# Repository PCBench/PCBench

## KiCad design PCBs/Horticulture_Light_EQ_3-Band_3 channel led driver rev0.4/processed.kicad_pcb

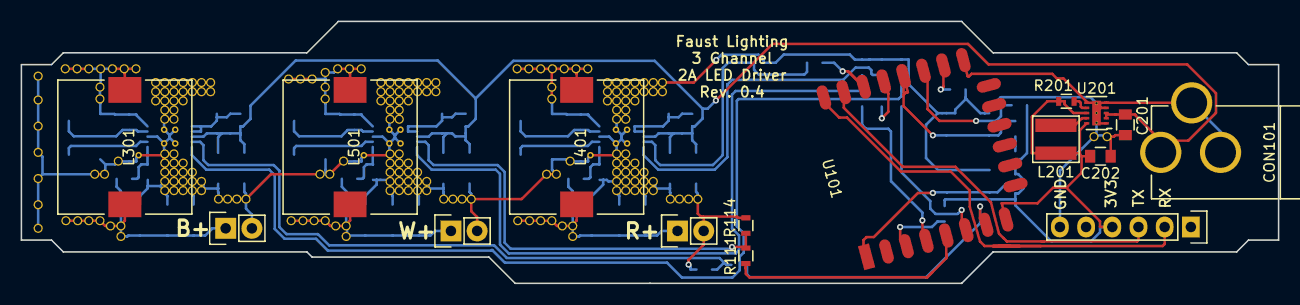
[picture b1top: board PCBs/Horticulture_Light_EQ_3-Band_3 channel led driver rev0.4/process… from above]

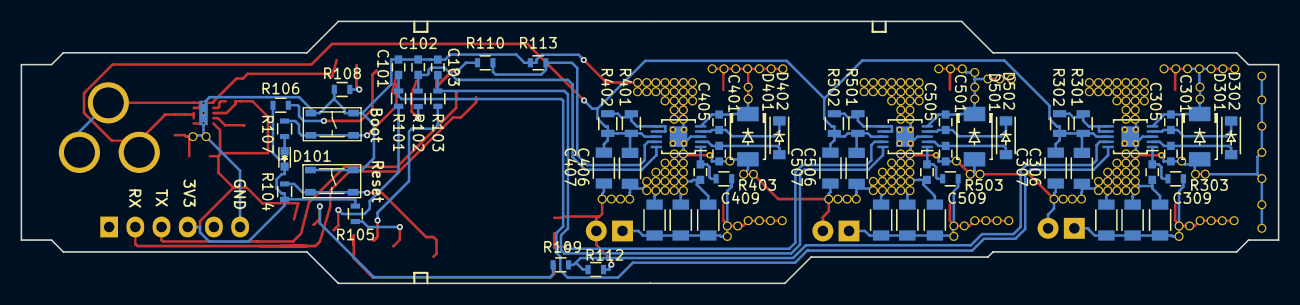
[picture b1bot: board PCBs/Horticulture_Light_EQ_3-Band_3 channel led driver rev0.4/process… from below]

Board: 2 copper layers, 121.9 x 25.4 mm, 76 parts (60 on the bottom side), 42 nets.

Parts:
C101, C102, C103: 10uF; C_0603
C201: 2.2uF; C_0805
C202: 22.0uF; C_0805
C301, C401, C501: 0.1uF; C_0603
C302, C303, C304, C306, C307, C402, C403, C404, C406, C407, C502, C503, C504, C506, C507: 2.2uF; C_1206
C305, C405, C505: 1uF; C_0603
C309, C409, C509: 470pF; C_0603
CON101: BARREL_JACK; Barrel_Jack_Wurth_694106301002
D101: LED; LED-0603
D301, D401, D501: 100V 3A; SOD-128-2
D302, D402, D502: 100V 200mA; SOD-123
L201: 10uH; VLS4012ET-100M
L301, L401, L501: 47uH; MBH12575C
P1, P2, P3: CONN_01X02; Pin_Header_Straight_1x02
P101: CONN_01X06; Pin_Header_Straight_1x06
R101, R102, R103, R107, R109, R110, R111: 1K; R_0603
R104, R105, R106, R108, R112, R113, R114: 10K; R_0603
R201: 100K; R_0603
R301, R302, R401, R402, R501, R502: 0.27; R_0805
R303, R403, R503: 48.7k; R_0603
SW101, SW102: TACT_4.2MM; MF_Switches-TACT4.2MM
U101: ESP8266-12E; ESP-12E
U201: TPS62177
U301, U401, U501: TPS92515; TPS92515x

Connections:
3V3: C202.1, D101.2, L201.2, P101.4, R104.2, R105.2, R106.2, R201.1, U101.8, U201.8, U201.10
+24V: C201.1, C306.1, C307.1, C406.1, C407.1, C506.1, C507.1, CON101.1, R301.1, R302.1, R401.1, R402.1, R501.1, R502.1, U201.2, U201.3, U301.8, U401.8, U501.8
/BOOT: R107.1, SW101.P$1, SW101.P$2, U101.18
/Blue_1.5A_Set/Analog_Control: C101.1, R101.1, U301.10
/Blue_1.5A_Set/PWM_Control: R109.2, R112.2, U301.9
/ENABLE: R105.1, U101.3
/GPIO2: R106.1, U101.17
/GPIO15: R108.2, U101.16
/RESET: R104.1, SW102.P$1, SW102.P$2, U101.1
/RX: P101.3, U101.21
/Red_1.5A_Set/Analog_Control: C102.1, R102.1, U401.10
/Red_1.5A_Set/PWM_Control: R110.2, R113.2, U401.9
/TX: P101.2, U101.22
/White_1.5A_Set/Analog_Control: C103.1, R103.1, U501.10
/White_1.5A_Set/PWM_Control: R111.2, R114.2, U501.9
BDIM: R101.2, U101.6
BLED+: C302.1, C303.1, C304.1, L301.1, P1.1, R303.2
BLED-: C101.2, C102.2, C103.2, C201.2, C202.2, C302.2, C303.2, C304.2, C305.1, C306.2, C307.2, C309.2, C402.2, C403.2, C404.2, C405.1, C406.2, C407.2, C409.2, C502.2, C503.2, C504.2, C505.1, C506.2, C507.2, C509.2, CON101.2, CON101.3, D301.2, D401.2, D501.2, P1.2, P2.2, P3.2, P101.6, R108.1, R112.1, R113.1, R114.1, SW101.P$3, SW101.P$4, SW102.P$3, SW102.P$4, U101.15, U201.1, U201.4, U201.5, U201.6, U201.11, U301.3, U301.11, U401.3, U401.11, U501.3, U501.11
BPWM: R109.1, U101.7
unnamed: C301.1, D301.1, L301.2, U301.5
unnamed: C301.2, D302.1, U301.4
unnamed: C305.2, D302.2, U301.2
unnamed: C309.1, R303.1, U301.1
unnamed: C401.1, D401.1, L401.2, U401.5
unnamed: C401.2, D402.1, U401.4
unnamed: C405.2, D402.2, U401.2
unnamed: C409.1, R403.1, U401.1
unnamed: C501.1, D501.1, L501.2, U501.5
unnamed: C501.2, D502.1, U501.4
unnamed: C505.2, D502.2, U501.2
unnamed: C509.1, R503.1, U501.1
unnamed: L201.1, U201.9
unnamed: R201.2, U201.7
unnamed: R301.2, R302.2, U301.6, U301.7
unnamed: R401.2, R402.2, U401.6, U401.7
unnamed: R501.2, R502.2, U501.6, U501.7
RDIM: R102.2, U101.19
RLED+: C402.1, C403.1, C404.1, L401.1, P2.1, R403.2
RPWM: R110.1, U101.20
WDIM: R103.2, U101.4
WLED+: C502.1, C503.1, C504.1, L501.1, P3.1, R503.2
WPWM: R111.1, U101.5

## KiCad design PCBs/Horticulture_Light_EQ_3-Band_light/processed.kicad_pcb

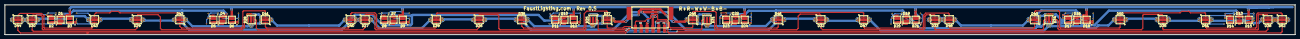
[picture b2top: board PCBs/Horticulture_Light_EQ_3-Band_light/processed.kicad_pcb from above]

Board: 2 copper layers, 551.2 x 12.7 mm, 53 parts (0 on the bottom side), 47 nets.

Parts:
D1, D2, D3, D4, D5, D6, D7, D8, D9, D10, D11, D12, D13, D14, D15, D16, D17, D18, D19, D20, D21, D22, D23, D24: Led_Small; MP3030
D25, D26, D27, D28, D29, D30, D31, D32, D33, D34, D35, D36: Blue 450nm; Blue_450nm
D37, D38, D39, D40, D41, D42, D43, D44, D45, D46, D47, D48, D49, D50, D51, D52: Deep Red 660nm; Deep_Red_660nm
P1: CONN_02X03; 1814676

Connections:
B+: D25.2, D31.2, P1.5
B-: D30.1, D36.1, P1.6
unnamed: D1.1, D2.2
unnamed: D2.1, D3.2
unnamed: D4.1, D5.2
unnamed: D5.1, D6.2
unnamed: D7.1, D8.2
unnamed: D8.1, D9.2
unnamed: D10.1, D11.2
unnamed: D11.1, D12.2
unnamed: D13.1, D14.2
unnamed: D14.1, D15.2
unnamed: D16.1, D17.2
unnamed: D17.1, D18.2
unnamed: D19.1, D20.2
unnamed: D20.1, D21.2
unnamed: D22.1, D23.2
unnamed: D23.1, D24.2
unnamed: D25.1, D26.2
unnamed: D26.1, D27.2
unnamed: D27.1, D28.2
unnamed: D28.1, D29.2
unnamed: D29.1, D30.2
unnamed: D31.1, D32.2
unnamed: D32.1, D33.2
unnamed: D33.1, D34.2
unnamed: D34.1, D35.2
unnamed: D35.1, D36.2
unnamed: D37.1, D38.2
unnamed: D38.1, D39.2
unnamed: D39.1, D40.2
unnamed: D40.1, D41.2
unnamed: D41.1, D42.2
unnamed: D42.1, D43.2
unnamed: D43.1, D44.2
unnamed: D45.1, D46.2
unnamed: D46.1, D47.2
unnamed: D47.1, D48.2
unnamed: D48.1, D49.2
unnamed: D49.1, D50.2
unnamed: D50.1, D51.2
unnamed: D51.1, D52.2
R+: D37.2, D45.2, P1.1
R-: D44.1, D52.1, P1.2
THERMAL: D25.3, D26.3, D27.3, D28.3, D29.3, D30.3, D31.3, D32.3, D33.3, D34.3, D35.3, D36.3, D37.3, D38.3, D39.3, D40.3, D41.3, D42.3, D43.3, D44.3, D45.3, D46.3, D47.3, D48.3, D49.3, D50.3, D51.3, D52.3
W+: D1.2, D4.2, D7.2, D10.2, D13.2, D16.2, D19.2, D22.2, P1.3
W-: D3.1, D6.1, D9.1, D12.1, D15.1, D18.1, D21.1, D24.1, P1.4

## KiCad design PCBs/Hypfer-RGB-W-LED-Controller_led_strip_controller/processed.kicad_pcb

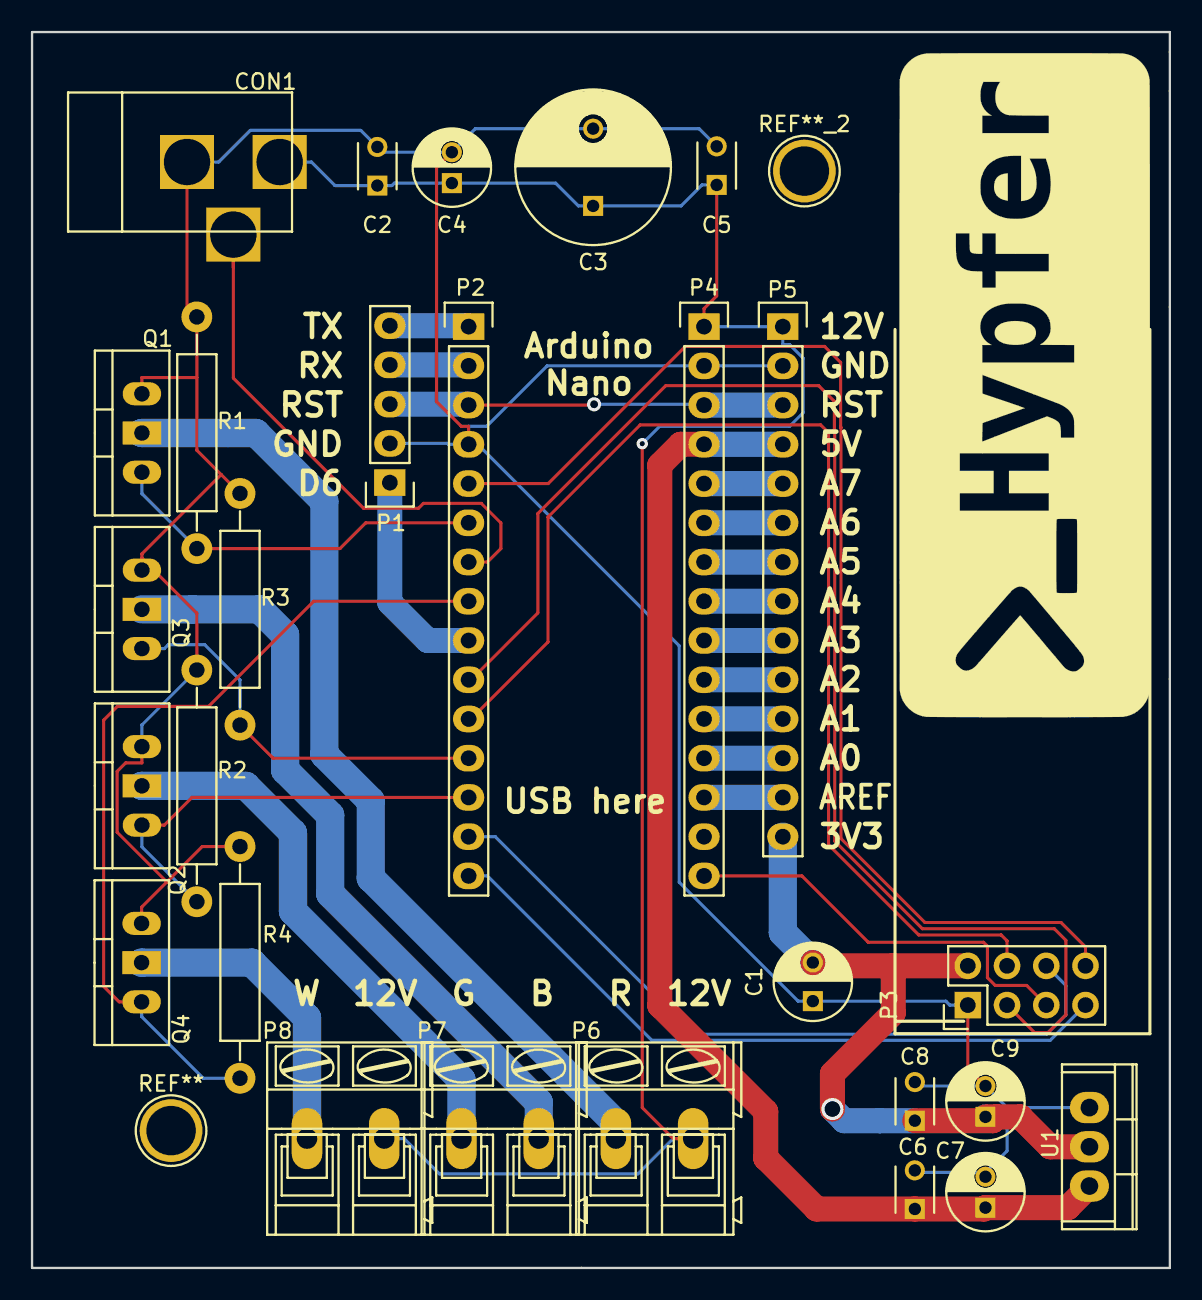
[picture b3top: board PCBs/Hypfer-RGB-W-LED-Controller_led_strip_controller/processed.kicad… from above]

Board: 2 copper layers, 73.7 x 80.0 mm, 27 parts (0 on the bottom side), 32 nets.

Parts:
C1: 1uF; C_Radial_D5_L11_P2.5
C2, C5, C6, C8: 100nF; C_Disc_D3_P2.5
C3: 1000uF; C_Radial_D10_L20_P5
C4, C7, C9: 47uF; C_Radial_D5_L11_P2
CON1: BARREL_JACK
P1: CONN_01X05; Socket_Strip_Straight_1x05
P2, P4: CONN_01X15; Socket_Strip_Straight_1x15
P3: CONN_02X04; Pin_Header_Straight_2x04
P5: CONN_01X14; Socket_Strip_Straight_1x14
P6, P7, P8: CONN_01X02; AK300-2
Q1, Q2, Q3, Q4: Q_NMOS_GDS; Diode_TO-220_Dual_CommonCathode_Vertical
R1, R2, R3, R4: 10k; Resistor_Horizontal_RM15mm
U1: AP1117; TO-220

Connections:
+3V3: C1.2, C8.1, C9.1, P3.2, P5.14, U1.2
+5V: C6.1, C7.1, P4.4, P5.4, U1.3
+12V: C2.1, C3.1, C4.1, C5.1, CON1.1, P4.1, P5.1, P6.2, P8.2
/ADC0: P4.12, P5.12
/ADC1: P4.11, P5.11
/ADC2: P4.10, P5.10
/ADC3: P4.9, P5.9
/ADC4: P4.8, P5.8
/ADC5: P4.7, P5.7
/ADC6: P4.6, P5.6
/ADC7: P4.5, P5.5
/AREF: P4.13, P5.13
/D6: P1.1, P2.9
/RESET: P1.3, P2.3, P4.3, P5.3
/RX: P1.4, P2.2
/TX: P1.5, P2.1
FET_B: P2.12, Q3.1, R3.1
FET_G: P2.13, Q2.1, R2.1
FET_R: P2.6, Q1.1, R1.1
FET_W: P2.8, Q4.1, R4.1
GND: C1.1, C2.2, C3.2, C4.2, C5.2, C6.2, C7.2, C8.2, C9.2, CON1.2, P1.2, P2.4, P3.1, P4.2, P5.2, Q1.3, Q2.3, Q3.3, Q4.3, R1.2, R2.2, R3.2, R4.2, U1.1
JACK_SW: CON1.3, P2.7
LED_B: P7.2, Q3.2
LED_G: P7.1, Q2.2
LED_R: P6.1, Q1.2
LED_W: P8.1, Q4.2
MISO: P2.15, P3.7
MOSI: P2.14, P3.6
SCK: P3.5, P4.15
nRF_CE: P2.10, P3.3
nRF_CSN: P2.11, P3.4
nRF_IRQ: P2.5, P3.8

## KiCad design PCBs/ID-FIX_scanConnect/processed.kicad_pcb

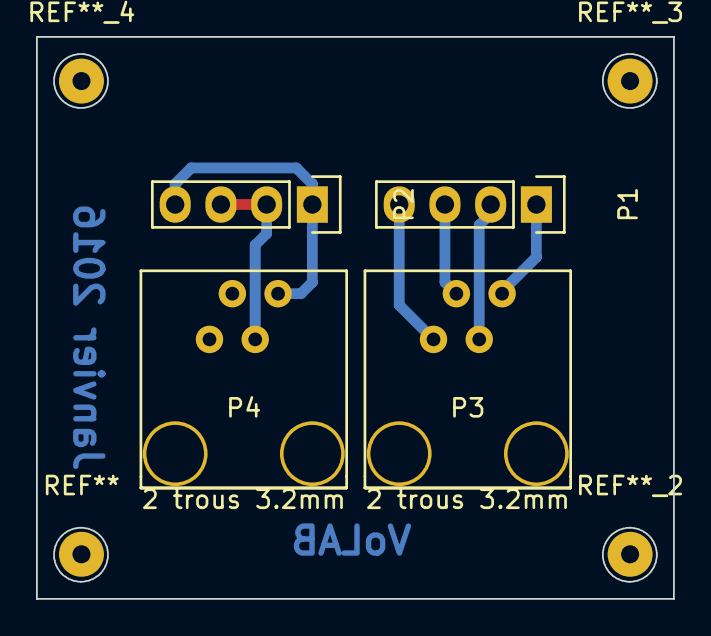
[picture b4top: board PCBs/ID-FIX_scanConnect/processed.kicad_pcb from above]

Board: 2 copper layers, 35.4 x 31.2 mm, 4 parts (0 on the bottom side), 6 nets.

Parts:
P1, P2: CONN_01X04; Pin_Header_Straight_1x04
P3, P4: RJ9

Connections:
/COILA_A: P1.1, P3.1
/COILA_B: P1.2, P3.2
/COILB_A: P1.3, P3.3
/COILB_B: P1.4, P3.4
/GND: P2.2, P2.3, P4.2
/VCC: P2.1, P2.4, P4.1

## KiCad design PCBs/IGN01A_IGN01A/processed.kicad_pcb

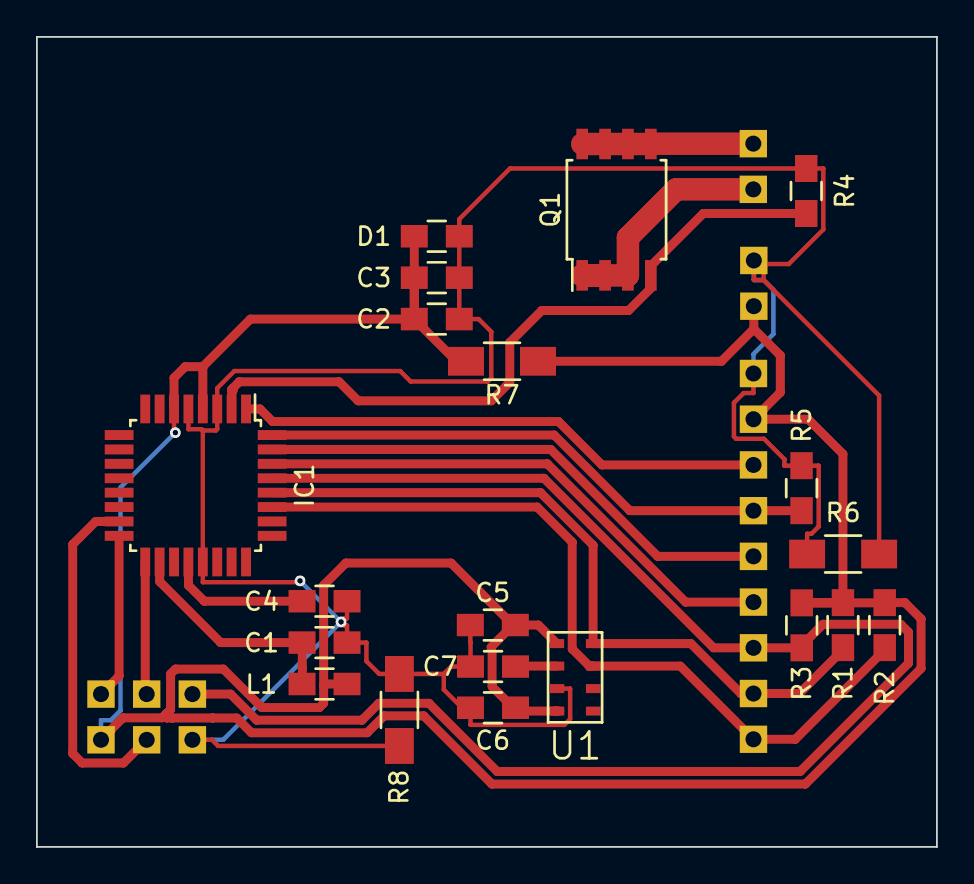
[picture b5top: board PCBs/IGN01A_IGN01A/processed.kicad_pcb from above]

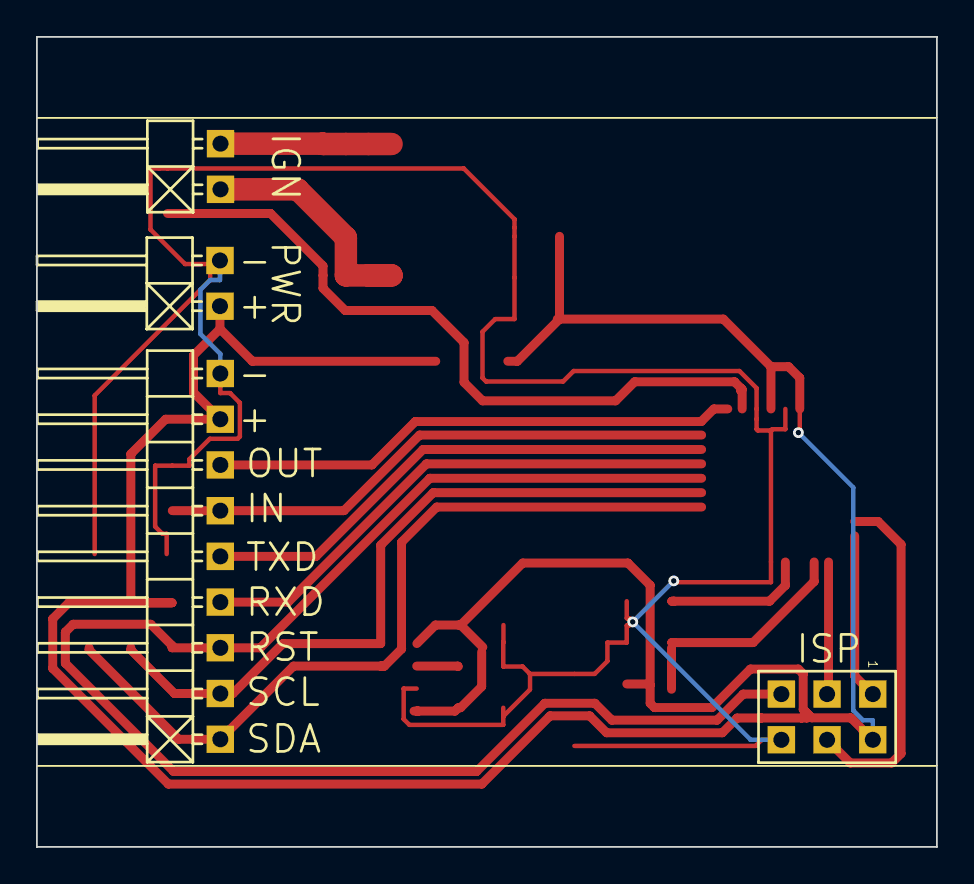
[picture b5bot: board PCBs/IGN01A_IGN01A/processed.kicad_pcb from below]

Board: 2 copper layers, 50.0 x 45.0 mm, 24 parts (4 on the bottom side), 18 nets.

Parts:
C1, C2, C4, C6, C7: 100nF; C_0805_HandSoldering
C3: 22uF/6.3V; C_0805_HandSoldering
C5: 10uF; C_0805_HandSoldering
D1: 1N4007; C_0805_HandSoldering
IC1: ATMEGA328-A; TQFP-32_7x7mm_Pitch0.8mm
J1: PWR; Angled_1x02
J2: IGN; Angled_1x02
J3: HEADER_1x09; Angled_1x09
J5: ISP; Straight_2x03
L1: 10uH; C_0805_HandSoldering
Q1: IRF7413ZPBF; SOIJ-8_5.3x5.3mm_Pitch1.27mm
R1, R2, R3, R4, R5: 10k; C_0805_HandSoldering
R6, R7, R8: 0; C_1206_HandSoldering
U1: MPL3115A2; LGA-MPL3115A

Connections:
/IGN: IC1.2, Q1.4, R4.1
/IN: IC1.32, J3.6, R5.1
/MISO: IC1.16, J5.1
/MOSI: IC1.15, J5.4
/OUT: IC1.1, J3.7
/RST: IC1.29, J3.3, J5.5, R3.2
/RXD: IC1.30, J3.4
/SCK: IC1.17, J5.3
/SCL: IC1.28, J3.2, R1.2, U1.8
/SDA: IC1.27, J3.1, R2.2, U1.7
/TXD: IC1.31, J3.5
GND: C1.2, C2.2, C3.2, C4.2, C5.2, C6.2, C7.2, D1.2, IC1.3, IC1.5, IC1.21, J1.2, J3.9, J5.6, R4.2, R5.2, R6.1, R6.2, R8.1, R8.2, U1.3
unnamed: C4.1, IC1.20
unnamed: C7.1, U1.2
unnamed: J2.1, Q1.1, Q1.2, Q1.3
unnamed: J2.2, Q1.5, Q1.6, Q1.7, Q1.8
VAA: C1.1, IC1.18, L1.1
VDD: C2.1, C3.1, C5.1, C6.1, D1.1, IC1.4, IC1.6, J1.1, J3.8, J5.2, L1.2, R1.1, R2.1, R3.1, R7.1, R7.2, U1.1, U1.4

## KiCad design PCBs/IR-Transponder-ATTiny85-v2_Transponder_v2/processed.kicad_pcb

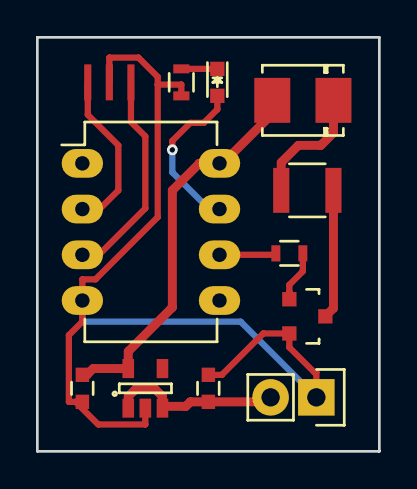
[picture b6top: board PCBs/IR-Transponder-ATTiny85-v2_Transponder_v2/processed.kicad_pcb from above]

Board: 2 copper layers, 19.0 x 23.0 mm, 12 parts (0 on the bottom side), 11 nets.

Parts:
C1, C2: .1u; C_0603
D1: LED; DO-214BA
D2: LED; LED_0603
IC1: ATTINY85-S; DIP-8_W7.62mm_LongPads
P1: CONN_01X02; Pin_Header_Straight_1x02
Q1: NMOS; SOT-23
R1, R3: 470; R_0603
R2: 100; R_1210
U1: 5.5v Reg; SOT-23-5
X1: CRYSTAL_SMD; myResonator

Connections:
+5V: C2.1, D1.2, IC1.8, U1.5
GND: C1.2, C2.2, IC1.4, P1.1, Q1.2, R3.2, U1.2, X1.3
unnamed: C1.1, P1.2, U1.1, U1.3
unnamed: D1.1, R2.1
unnamed: D2.1, R3.1
unnamed: IC1.2, X1.1
unnamed: IC1.3, X1.2
unnamed: Q1.1, R1.2
unnamed: Q1.3, R2.2
PB1: IC1.6, R1.1
PB2: D2.2, IC1.7

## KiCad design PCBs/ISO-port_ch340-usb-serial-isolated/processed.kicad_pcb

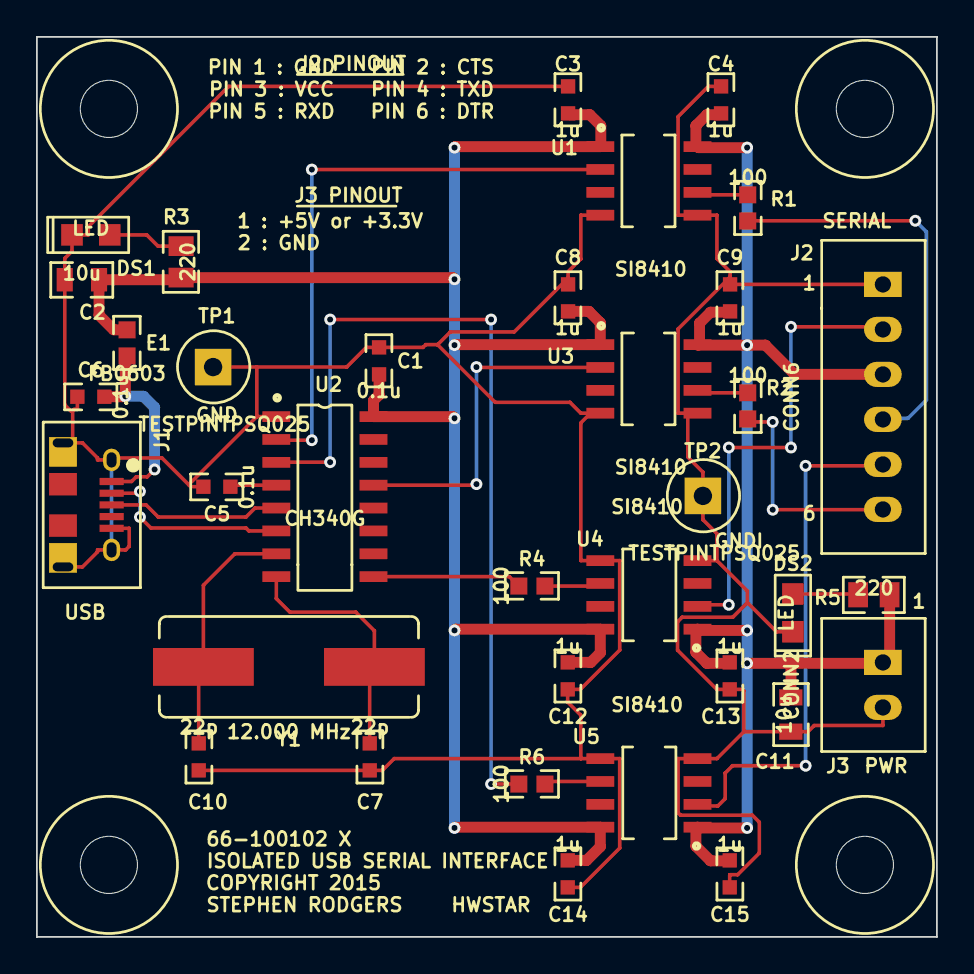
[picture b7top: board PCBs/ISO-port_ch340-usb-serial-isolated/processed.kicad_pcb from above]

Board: 2 copper layers, 50.0 x 50.0 mm, 39 parts (0 on the bottom side), 24 nets.

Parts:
C1, C5, C6: 0.1u; CC0603
C2, C11: 10u; CC0805
C3, C4, C8, C9, C12, C13, C14, C15: 1u; CC0603
C7, C10: 22p; CC0603
DS1, DS2: LED; LED0805
E1: FB0603; RC0603
J1: CONN-USB-B-MICRO-FCI-11018194
J2: CONN6; JST_B6B_XH_A
J3: CONN2; JST_B2B_XH_A
MTG-HOLE-125-RING-300, MTG-HOLE-125-RING-300_2, MTG-HOLE-125-RING-300_3, MTG-HOLE-125-RING-300_4: VAL**; MTG-HOLE-125-RING-300
R1, R2, R4, R6: 100; RC0603
R3, R5: 220; RC0805
TP1, TP2: TESTPINTPSQ025; TESTPIN
U1, U3, U4, U5: SI8410; SOIC8N-SI8410
U2: CH340G; SOIC16N-SAR
Y1: 12.000 MHz; HC49US-SAR

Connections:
+5V: C1.1, C2.1, C3.1, C8.1, C12.1, C14.1, E1.2, R3.1, U1.1, U2.16, U3.1, U4.8, U5.8
+5VI: C4.1, C9.1, C11.1, C13.1, C15.1, J2.3, J3.1, R5.1, U1.8, U3.8, U4.1, U5.1
/CTSI: J2.2, U4.2
/CTSU: R4.1, U2.9
/D+: J1.3, U2.5
/D-: J1.2, U2.6
/DTRI: J2.6, R2.2
/DTRU: U2.13, U3.2
/RXDI: J2.5, U5.2
/RXDU: R6.1, U2.3
/TXDI: J2.4, R1.2
/TXDU: U1.2, U2.2
/VBUS: C6.1, E1.1, J1.1
GND: C1.2, C2.2, C3.2, C5.2, C6.2, C7.2, C8.2, C10.2, C12.2, C14.2, DS1.2, J1.5, J1.6, J1.7, J1.8, J1.9, TP1.1, U1.4, U2.1, U3.4, U4.5, U5.5
GNDI: C4.2, C9.2, C11.2, C13.2, C15.2, DS2.2, J2.1, J3.2, TP2.1, U1.5, U3.5, U4.4, U5.4
unnamed: R1.1, U1.6
unnamed: R6.2, U5.6
unnamed: DS2.1, R5.2
unnamed: DS1.1, R3.2
unnamed: R2.1, U3.6
unnamed: R4.2, U4.6
unnamed: C10.1, U2.7, Y1.1
unnamed: C5.1, U2.4
unnamed: C7.1, U2.8, Y1.2

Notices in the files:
PCBs/ISO-port_ch340-usb-serial-isolated/processed.kicad_pcb:
COPYRIGHT 2015
